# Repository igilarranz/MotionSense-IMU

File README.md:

# MotionSense IMU

MotionSense IMU is a custom 2-layer PCB built around the ST LSM6DSM 6-axis accelerometer and gyroscope.

The board takes 5 V from USB-C, regulates it to 3.3 V, and breaks out the IMU's I2C interface and interrupt signal through a 5-pin header.

## Hardware

* LSM6DSM 6-axis accelerometer + gyroscope
* AP2112K-3.3 LDO regulator
* USB-C 5 V input
* 4.7 kΩ pull-up resistors on SDA and SCL
* Decoupling capacitors for the regulator and IMU
* 5-pin interface header
* 2-layer PCB
* Board size: approximately 35 mm × 27 mm

## Pinout

| Pin | Signal |
| --- | ------ |
| 1   | 3V3    |
| 2   | GND    |
| 3   | SDA    |
| 4   | SCL    |
| 5   | INT1   |

## Design

The schematic and PCB were designed in KiCad.

During routing, I experimented with Quilter and Freerouting before bringing the design back into KiCad for final cleanup and verification.

The final design passes KiCad DRC with:

* 0 violations
* 0 unconnected items

Gerber and drill files were generated and inspected before manufacturing.

## Schematic

The schematic includes the USB-C power input, AP2112K 3.3 V regulator, LSM6DSM IMU, I2C pull-up resistors, decoupling capacitors, and J2 breakout header.

The editable KiCad schematic is available in `MotionSense_IMU.kicad_sch`.

## PCB Layout

The board is a 2-layer design with USB-C power input on one side and the I2C breakout header on the opposite side.

## Manufacturing

Rev 1 was submitted to JLCPCB for fabrication and assembly in August 2026.

Five PCBs were ordered, with two boards receiving component assembly.

The 1×5 J2 header is intentionally left unpopulated and will be soldered manually during bring-up.

## Files

* `MotionSense_IMU.kicad_pcb` — KiCad PCB layout
* `MotionSense_IMU.kicad_pro` — KiCad project
* `MotionSense_IMU.kicad_sch` — KiCad schematic
* `BOM.csv` — bill of materials
* `MotionSense_IMU_Rev1_Gerbers.zip` — Gerber and drill files
* `pcb_3D.png` — 3D board render
* `pcb_layout.png` — PCB layout image
* `schematic.png` — schematic image

## Fabrication Files

The Rev 1 Gerber and drill files used for manufacturing are included in the repository.

[Download Gerber + drill files](https://github.com/igilarranz/MotionSense-IMU/raw/refs/heads/main/MotionSense_IMU_Rev1_Gerbers.zip)

## Current Status

**Rev 1 has been ordered for fabrication and assembly.**

The PCB design and manufacturing files are complete. The next stage is hardware bring-up and firmware validation once the assembled boards arrive.

## Bring-Up Plan

1. Inspect the assembled board for soldering or placement issues.
2. Solder the J2 header.
3. Check for shorts between 3.3 V and GND.
4. Power the board through USB-C.
5. Verify the 5 V input and 3.3 V regulator output with a multimeter.
6. Connect an ESP32 to SDA, SCL, and GND.
7. Detect the LSM6DSM over I2C.
8. Read the `WHO_AM_I` register to confirm communication.
9. Read live accelerometer and gyroscope data.
10. Test the INT1 interrupt output.

## Next Steps

* Prepare ESP32 bring-up firmware
* Complete electrical testing
* Validate accelerometer and gyroscope measurements
* Test interrupt functionality
* Document test results
* Record any changes needed for Rev 2

## Project Goal

The goal of this project is to work through the complete PCB development process, from schematic capture and component selection through layout, manufacturing, assembly, and hardware validation.

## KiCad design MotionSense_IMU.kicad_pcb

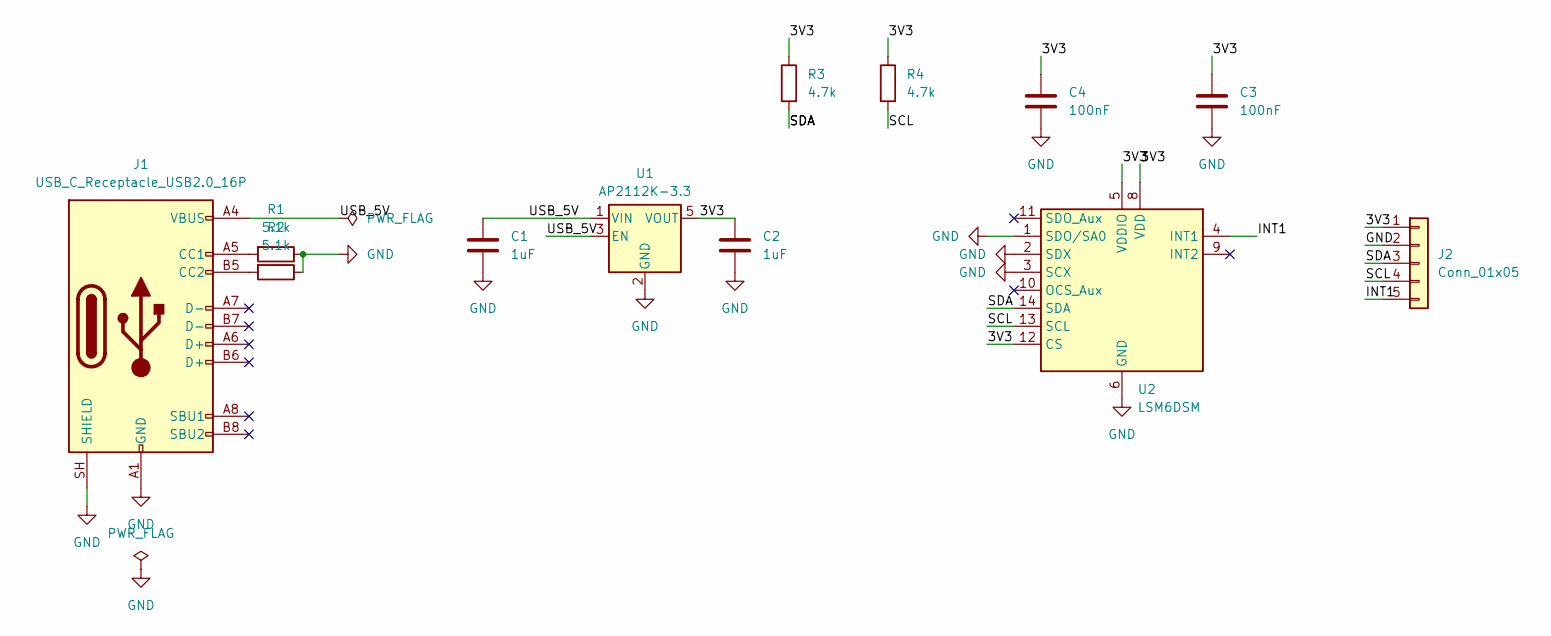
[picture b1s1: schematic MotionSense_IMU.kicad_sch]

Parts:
C1, C2: 1uF; C_0603_1608Metric_Pad1.08x0.95mm_HandSolder
C3, C4: 100nF; C_0603_1608Metric_Pad1.08x0.95mm_HandSolder
J1: USB_C_Receptacle_USB2.0_16P; USB_C_Receptacle_GCT_USB4105-xx-A_16P_TopMnt_Horizontal
J2: Conn_01x05; PinHeader_1x05_P2.54mm_Vertical
R1, R2: 5.1k; R_0603_1608Metric_Pad0.98x0.95mm_HandSolder
R3, R4: 4.7k; R_0603_1608Metric_Pad0.98x0.95mm_HandSolder
U1: AP2112K-3.3; SOT-23-5
U2: LSM6DSM; LGA-14_3x2.5mm_P0.5mm_LayoutBorder3x4y

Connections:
/3V3: C2.1, C3.1, C4.1, J2.1, R3.1, R4.1, U1.5 (VOUT), U2.5 (VDDIO), U2.8 (VDD), U2.12 (CS)
/INT1: J2.5, U2.4 (INT1)
/SCL: J2.4, R4.2, U2.13 (SCL)
/SDA: J2.3, R3.2, U2.14 (SDA)
/USB_5V: C1.2, J1.A4 (VBUS), J1.A9 (VBUS), J1.B4 (VBUS), J1.B9 (VBUS), U1.1 (VIN), U1.3 (EN)
GND: C1.1, C2.2, C3.2, C4.2, J1.A1 (GND), J1.A12 (GND), J1.B1 (GND), J1.B12 (GND), J1.SH (SHIELD), J2.2, R1.1, R2.1, U1.2 (GND), U2.1 (SDO/SA0), U2.2 (SDX), U2.3 (SCX), U2.6 (GND), U2.7 (GND)
unnamed: J1.A5 (CC1), R1.2
unnamed: J1.B5 (CC2), R2.2

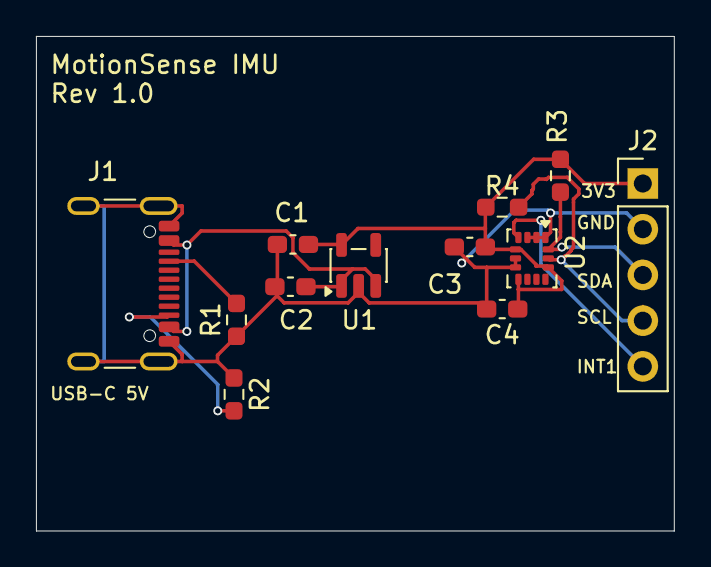
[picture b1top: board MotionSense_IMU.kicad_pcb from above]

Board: 2 copper layers, 35.4 x 27.5 mm, 12 parts (0 on the bottom side), 8 nets.

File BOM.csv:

Reference,Value,Footprint
C1,1uF,Capacitor_SMD:C_0603_1608Metric_Pad1.08x0.95mm_HandSolder
C2,1uF,Capacitor_SMD:C_0603_1608Metric_Pad1.08x0.95mm_HandSolder
C3,100nF,Capacitor_SMD:C_0603_1608Metric_Pad1.08x0.95mm_HandSolder
C4,100nF,Capacitor_SMD:C_0603_1608Metric_Pad1.08x0.95mm_HandSolder
J1,USB_C_Receptacle_USB2.0_16P,Connector_USB:USB_C_Receptacle_GCT_USB4105-xx-A_16P_TopMnt_Horizontal
J2,Conn_01x05,Connector_PinHeader_2.54mm:PinHeader_1x05_P2.54mm_Vertical
R1,5.1k,Resistor_SMD:R_0603_1608Metric_Pad0.98x0.95mm_HandSolder
R2,5.1k,Resistor_SMD:R_0603_1608Metric_Pad0.98x0.95mm_HandSolder
R3,4.7k,Resistor_SMD:R_0603_1608Metric_Pad0.98x0.95mm_HandSolder
R4,4.7k,Resistor_SMD:R_0603_1608Metric_Pad0.98x0.95mm_HandSolder
U1,AP2112K-3.3,Package_TO_SOT_SMD:SOT-23-5
U2,LSM6DSM,Package_LGA:LGA-14_3x2.5mm_P0.5mm_LayoutBorder3x4y
